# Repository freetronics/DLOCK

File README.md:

Freetronics RFID Door Lock Shield
==================================
Copyright 2013 Freetronics Pty Ltd  
Freetronics site:  www.freetronics.com  
Freetronics email: info@freetronics.com  

Based on the circuit described in the "RFID Access Control" project in
the book "Practical Arduino", this shield allows you to control a door
lock using an electric strike plate using a number of commonly
available RFID reader modules.

Supported reader modules include:

 * ID12
 * ID20
 * RDM630
 * RDM880
 * HF MultiTag

Features:

 * Reset button wired through to Arduino reset pin.
 * Blue "Arduino power on" LED with current-limiting resistor.
 * 100nF bypass/smoothing capacitor on supply rails.
 * Overlay guide where you need it: both top and bottom.

Compatible with the Freetronics TwentyTen, Arduino Uno, Arduino
Duemilanove, and other compatible boards based on the same header
format.

More information is available at:

  http://www.freetronics.com/dlock
  http://www.practicalarduino.com/projects/rfid-access-control

INSTALLATION
------------
The design is saved as an EAGLE project. EAGLE PCB design software is
available from www.cadsoftusa.com free for non-commercial use. To use
this project download it and place the directory containing these files
into the "eagle" directory on your computer. Then open EAGLE and
navigate to Projects -> eagle -> DLOCK.

DISTRIBUTION
------------
The specific terms of distribution of this project are governed by the
license referenced below.

LICENSE
-------
Licensed under the TAPR Open Hardware License (www.tapr.org/OHL).
The "license" folder within this repository also contains a copy of
this license in plain text format.

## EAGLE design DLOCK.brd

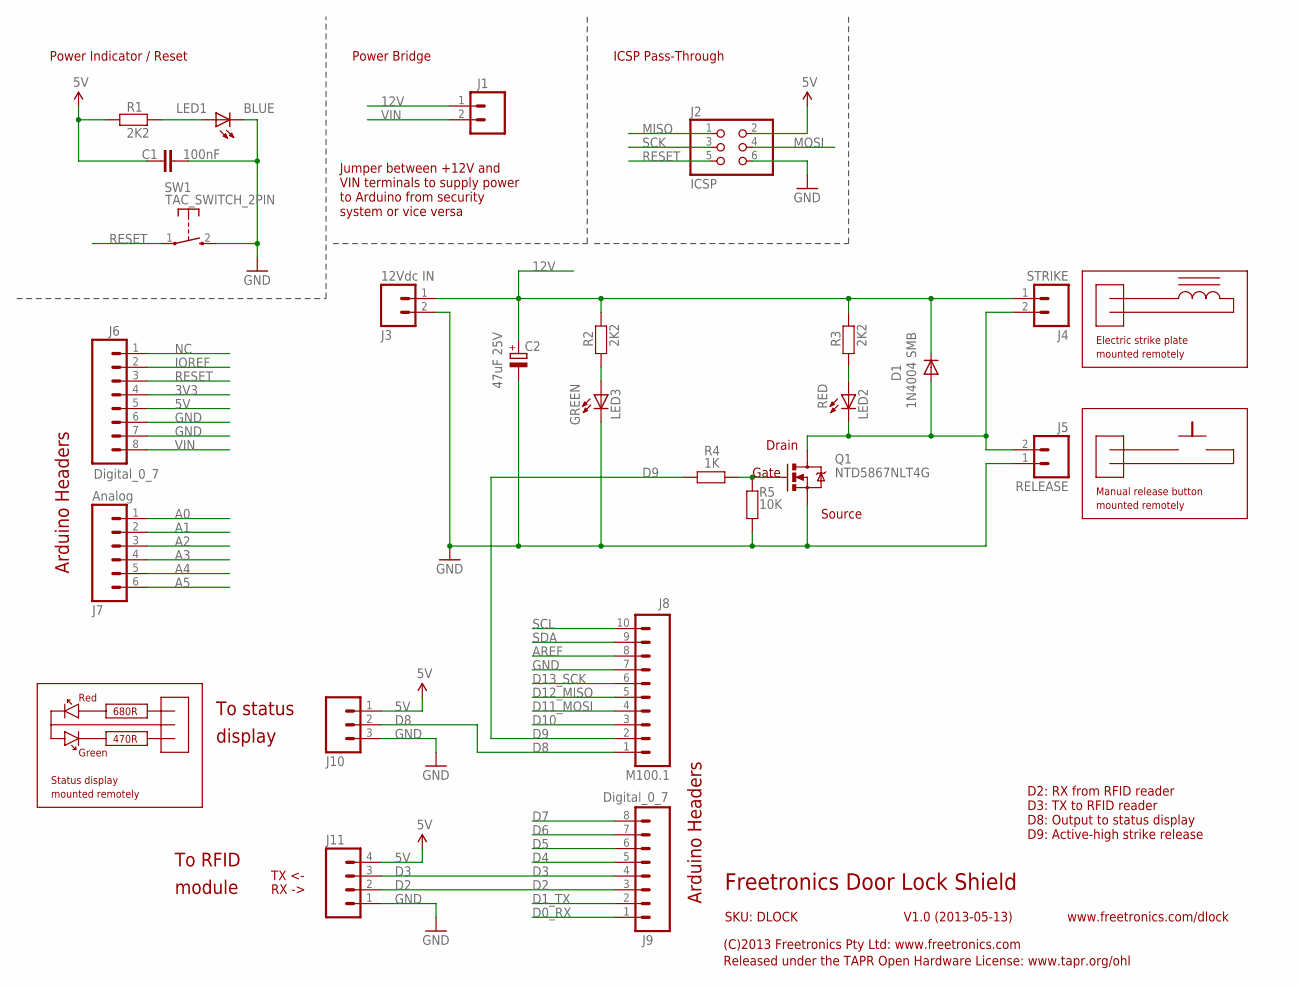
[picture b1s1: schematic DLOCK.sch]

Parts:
C1: 100nF; 0603
C2: 47uF 25V; PANASONIC_D
D1: 1N4004 SMB; SMB-DIODE
J1: M02PTH; 1X02
J2: ICSP; 2X03
J3: 12Vdc IN; SCREWTERMINAL-3.5MM-2
J4: STRIKE; SCREWTERMINAL-3.5MM-2
J5: RELEASE; 1X02
J6, J9: Digital_0_7; 1X08
J7: Analog; 1X06
J8: M100.1; 1X10
J10: M03PTH; 1X03
J11: M04PTH; 1X04
LED1: BLUE; LED-0603
LED2: RED; LED-0603
LED3: GREEN; LED-0603
Q1: NTD5867NLT4G; DPACK
R1, R2, R3: 2K2; 0603
R4: 1K; 0603
R5: 10K; 0603
SW1: TAC_SWITCH_2PIN; TACTILE_SWITCH_SMD_2PIN_TINY

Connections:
3V3: J6.4
5V: C1.1, J2.2, J6.5, J10.1, J11.4, R1.1
12V: C2.+, D1.C, J1.1, J3.1, J4.1, R2.2, R3.2
A0: J7.1
A1: J7.2
A2: J7.3
A3: J7.4
A4: J7.5
A5: J7.6
AREF: J8.8
D0_RX: J9.1
D1_TX: J9.2
D2: J9.3, J11.2
D3: J9.4, J11.3
D4: J9.5
D5: J9.6
D6: J9.7
D7: J9.8
D8: J8.1, J10.2
D9: J8.2, R4.2
D10: J8.3
D11_MOSI: J8.4
D12_MISO: J8.5
D13_SCK: J8.6
GND: C1.2, C2.-, J2.6, J3.2, J5.1, J6.6, J6.7, J8.7, J10.3, J11.1, LED1.C, LED3.C, Q1.3 (S), R5.1, SW1.2 (S)
IOREF: J6.2
MISO: J2.1
MOSI: J2.4
unnamed: D1.A, J4.2, J5.2, LED2.C, Q1.2 (D)
unnamed: LED2.A, R3.1
unnamed: Q1.1 (G), R4.1, R5.2
unnamed: LED3.A, R2.1
unnamed: LED1.A, R1.2
NC: J6.1
RESET: J2.5, J6.3, SW1.1
SCK: J2.3
SCL: J8.10
SDA: J8.9
VIN: J1.2, J6.8

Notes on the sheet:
Arduino Headers
To RFID
module
TX <-
RX ->
To status
display
680R
470R
Red
Green
Status display
mounted remotely
Manual release button
Electric strike plate
D2: RX from RFID reader D3: TX to RFID reader D8: Output to status display D9: Active-high strike release
Drain
Gate
Source
Freetronics Door Lock Shield
V1.0 (2013-05-13)
SKU: DLOCK
(C)2013 Freetronics Pty Ltd: www.freetronics.com
Released under the TAPR Open Hardware License: www.tapr.org/ohl
www.freetronics.com/dlock
Power Indicator / Reset
Power Bridge
Jumper between +12V and VIN terminals to supply power to Arduino from security system or vice versa
ICSP Pass-Through

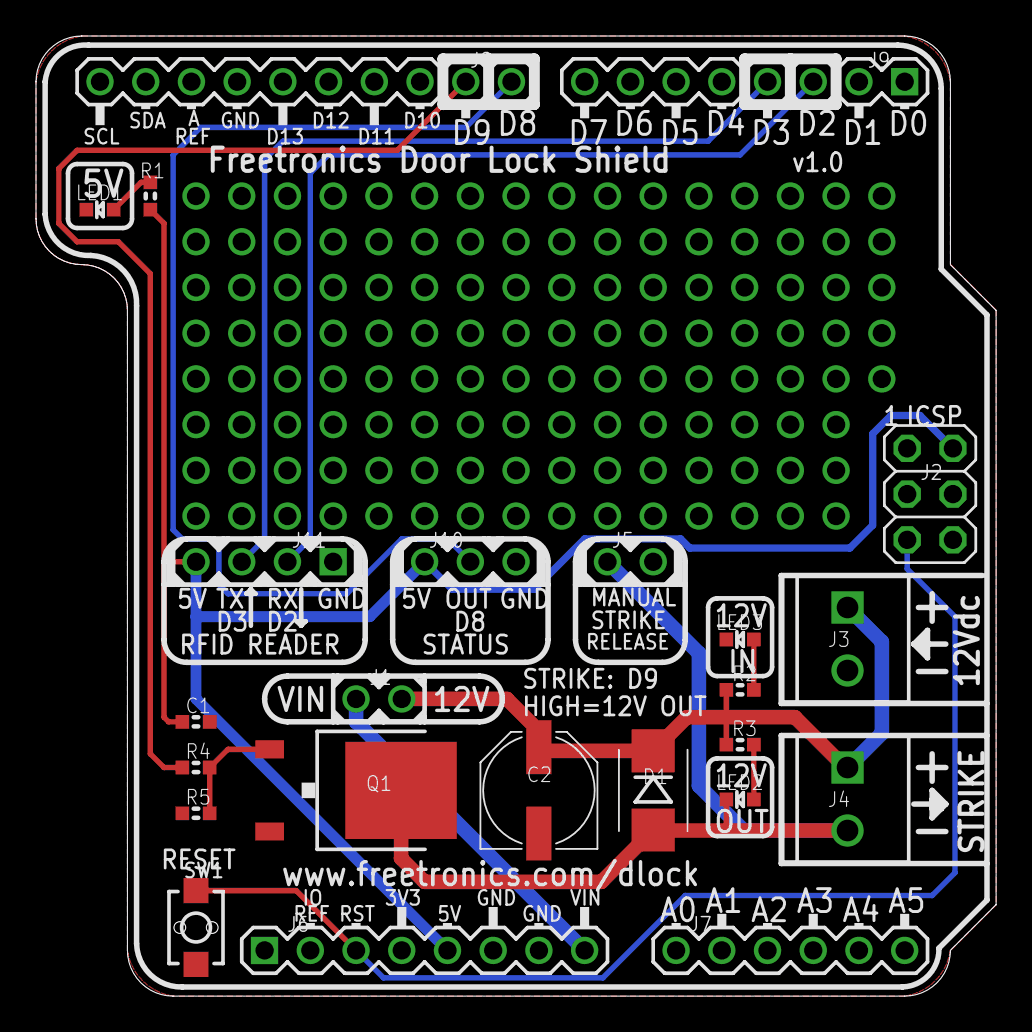
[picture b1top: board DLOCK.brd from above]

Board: 2 copper layers, 53.3 x 53.3 mm, 24 parts (0 on the bottom side), 14 nets.

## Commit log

2013-09-27 RFID Door Lock Shield v1.0 release
